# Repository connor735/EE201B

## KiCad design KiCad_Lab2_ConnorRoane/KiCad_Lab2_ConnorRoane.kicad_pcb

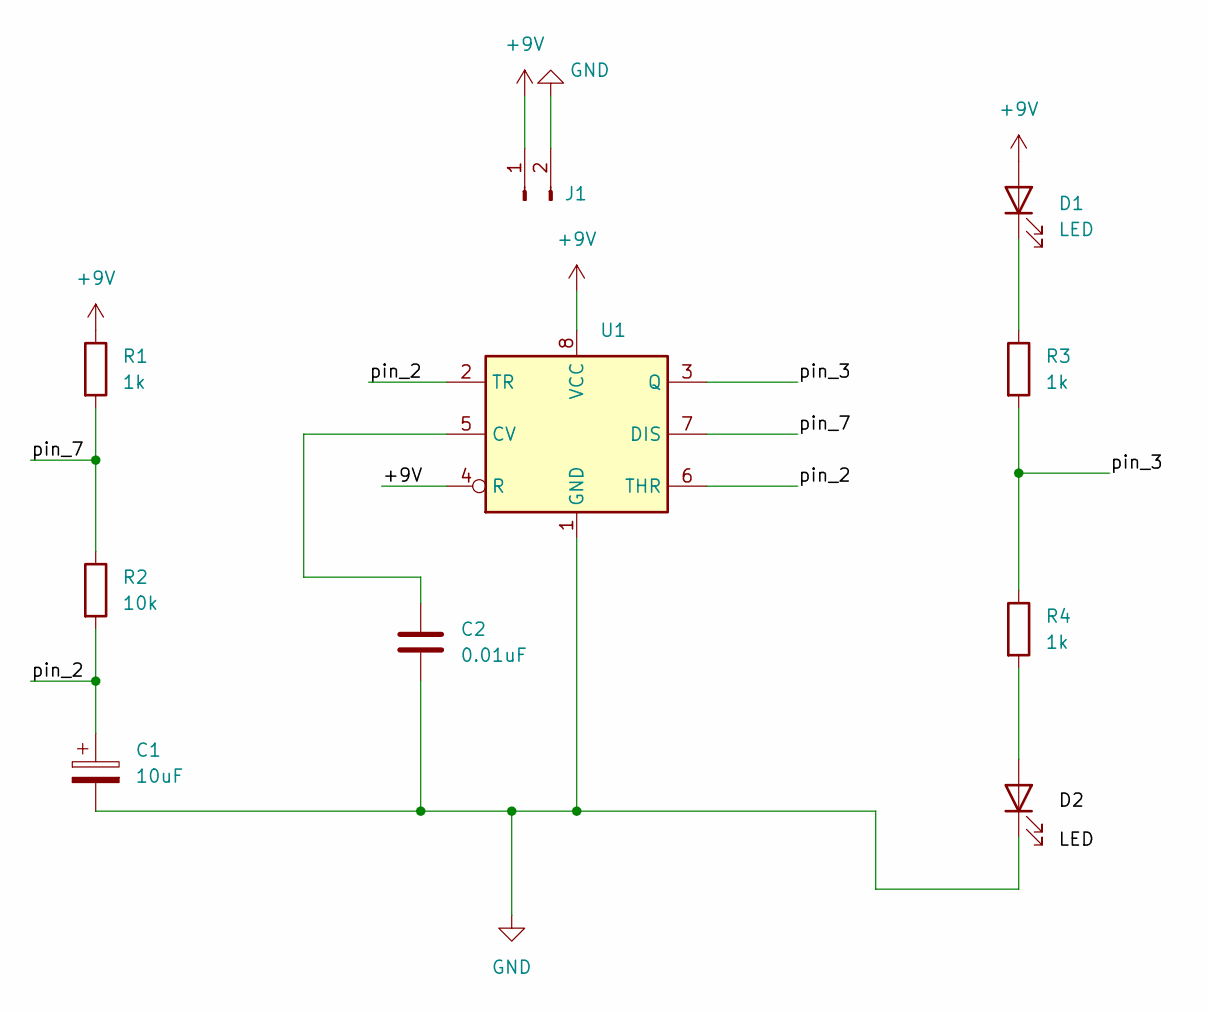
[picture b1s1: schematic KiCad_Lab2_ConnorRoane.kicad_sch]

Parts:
C1: 10uF; CP_EIA-3216-18_Kemet-A_Pad1.58x1.35mm_HandSolder
C2: 0.01uF; C_0805_2012Metric_Pad1.18x1.45mm_HandSolder
D1: LED
D2: LED; LED_1206_3216Metric_Pad1.42x1.75mm_HandSolder
J1: JST_EH_S2B-EH_1x02_P2.50mm_Horizontal
R1, R3, R4: 1k; R_0805_2012Metric_Pad1.20x1.40mm_HandSolder
R2: 10k; R_0805_2012Metric_Pad1.20x1.40mm_HandSolder
U1: SOIC-8-1EP_3.9x4.9mm_P1.27mm_EP2.29x3mm

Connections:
+9V: D1.2 (A), J1.1, R1.1, U1.4 (R), U1.8 (VCC)
/pin_2: C1.1, R2.2, U1.2 (TR), U1.6 (THR)
/pin_3: R3.2, R4.1, U1.3 (Q)
/pin_7: R1.2, R2.1, U1.7 (DIS)
GND: C1.2, C2.2, D2.1 (K), J1.2, U1.1 (GND)
unnamed: D1.1 (K), R3.1
unnamed: D2.2 (A), R4.2
unnamed: C2.1, U1.5 (CV)

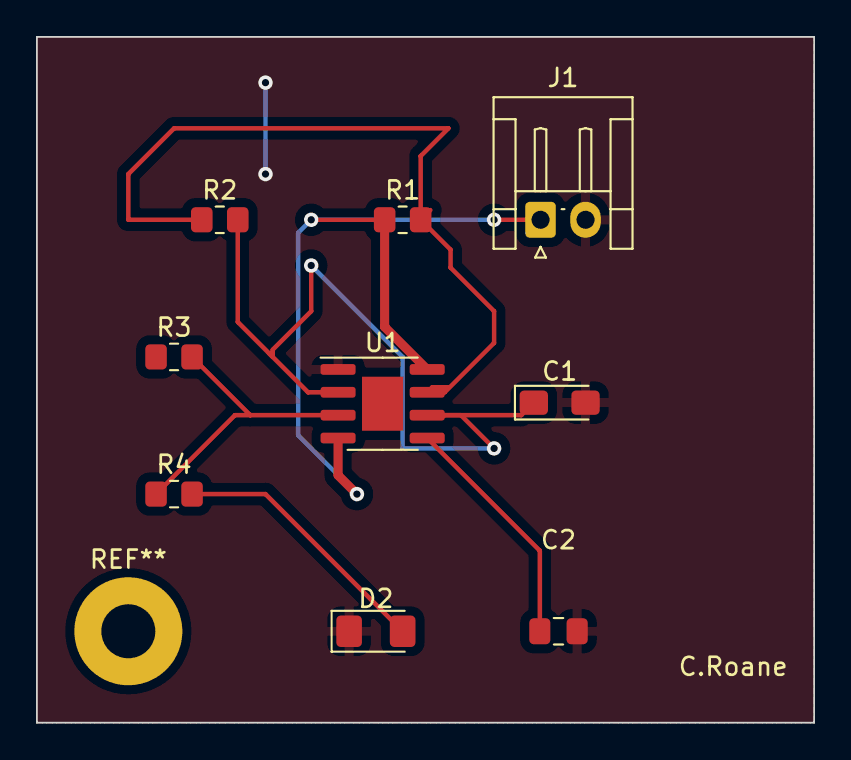
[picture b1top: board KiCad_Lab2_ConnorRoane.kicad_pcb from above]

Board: 2 copper layers, 43.2 x 38.1 mm, 9 parts (0 on the bottom side), 7 nets.

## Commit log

2023-10-23 my 3d part!
2023-10-23 3d model
2023-10-23 lab 4
2023-10-23 Arduino
2023-10-31 here are the soldering pictures
2023-12-09 here it is
2023-12-11 some files that might work
